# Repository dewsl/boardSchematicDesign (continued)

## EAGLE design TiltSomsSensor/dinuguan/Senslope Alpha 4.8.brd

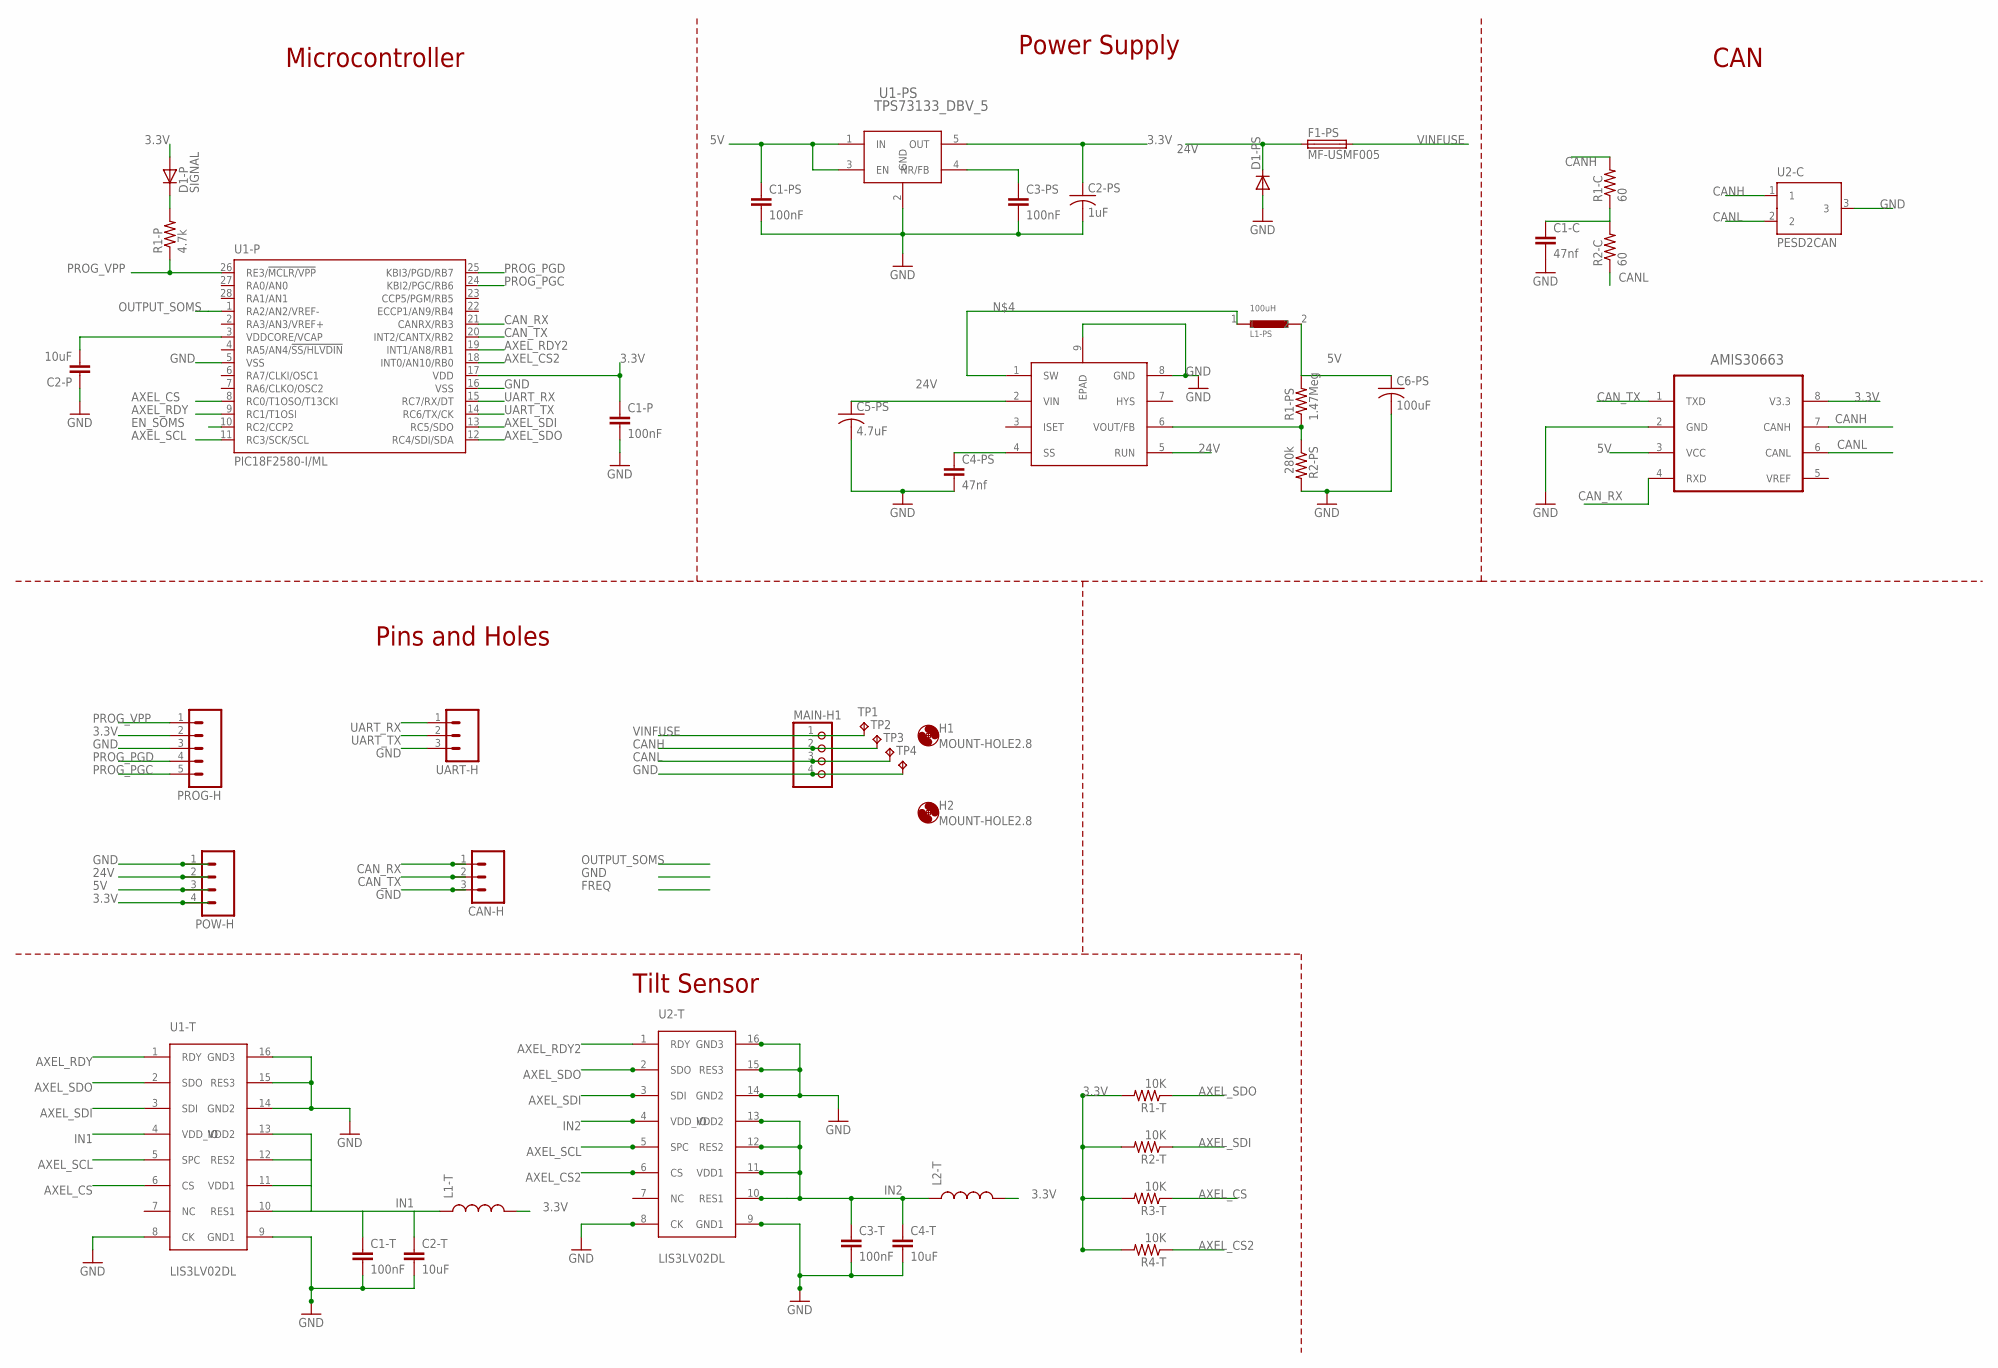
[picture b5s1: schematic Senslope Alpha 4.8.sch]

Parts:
C1-C, C4-PS: 47nf; C0805
C1-P, C1-PS, C3-PS: 100nF; C0603
C1-T, C3-T: 100nF; C0402
C2-P: 10uF; C0603
C2-PS: 1uF; C0402
C2-T, C4-T: 10uF; C0402
C5-PS: 4.7uF; C1206K
C6-PS: 100uF; C1210K
CAN-H: UART; 1X03_NO_SILK
D1-P: SIGNAL; DIODE-0603
D1-PS: DIODE-DO-214AC; DO-214AC
F1-PS: MF-USMF005; 1210
H1, H2: MOUNT-HOLE2.8; 2,8
L1-PS: 100uH; 1210
L1-T: H2; C0402
L2-T: H1; C0402
MAIN-H1: PINHD-1X04_2.54; 1X04
POW-H: M041X04_NO_SILK; 1X04_NO_SILK
PROG-H: M05PTH; 1X05
R1-C, R2-C: 60; R0805
R1-P: 4.7k; R0603
R1-PS: 1.47Meg; R0805
R1-T, R2-T, R3-T, R4-T: 10K; R0603
R2-PS: 280k; R0805
TP1, TP2, TP3, TP4: TPTP10SQ; TP10SQ
U1-P: PIC18F2580-I/ML; QFN28-ML_6X6MM
U1-PS: TPS73133_DBV_5; DBV5
U1-T, U2-T: LIS3LV02DL; LGA16
U2: AMIS30663CAN; SOIC8
U2-C: PESD2CAN; SOT23
U2-PS: LTC3631-5; MSOP8E
UART-H: UART; 1X03_NO_SILK

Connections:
3.3V: C1-P.1, C2-PS.1, D1-P.A, L1-T.2, L2-T.2, POW-H.4, PROG-H.2, R1-T.2, R2-T.2, R3-T.2, R4-T.2, U1-P.17 (VDD), U1-PS.5 (OUT), U2.8 (V3.3)
5V: C1-PS.1, C6-PS.1, L1-PS.2, POW-H.3, R1-PS.2, U1-PS.1 (IN), U1-PS.3 (EN), U2.3 (VCC)
24V: C5-PS.1, D1-PS.1 (C), F1-PS.1, POW-H.2, U2-PS.2 (VIN), U2-PS.5 (RUN)
AXEL_CS: R3-T.1, U1-P.8 (RC0/T1OSO/T13CKI), U1-T.6 (CS)
AXEL_CS2: R4-T.1, U1-P.18 (INT0/AN10/RB0), U2-T.6 (CS)
AXEL_RDY: U1-P.9 (RC1/T1OSI), U1-T.1 (RDY)
AXEL_RDY2: U1-P.19 (INT1/AN8/RB1), U2-T.1 (RDY)
AXEL_SCL: U1-P.11 (RC3/SCK/SCL), U1-T.5 (SPC), U2-T.5 (SPC)
AXEL_SDI: R2-T.1, U1-P.13 (RC5/SDO), U1-T.3 (SDI), U2-T.3 (SDI)
AXEL_SDO: R1-T.1, U1-P.12 (RC4/SDI/SDA), U1-T.2 (SDO), U2-T.2 (SDO)
CANH: MAIN-H1.2, R1-C.2, TP2.TP, U2.7 (CANH), U2-C.1
CANL: MAIN-H1.3, R2-C.1, TP3.TP, U2.6 (CANL), U2-C.2
CAN_RX: CAN-H.1, U1-P.21 (CANRX/RB3), U2.4 (RXD)
CAN_TX: CAN-H.2, U1-P.20 (INT2/CANTX/RB2), U2.1 (TXD)
EN_SOMS: U1-P.10 (RC2/CCP2)
GND: C1-C.2, C1-P.2, C1-PS.2, C1-T.2, C2-P.1, C2-PS.2, C2-T.2, C3-PS.2, C3-T.2, C4-PS.2, C4-T.2, C5-PS.2, C6-PS.2, CAN-H.3, D1-PS.2 (A), MAIN-H1.4, POW-H.1, PROG-H.3, R2-PS.2, TP4.TP, U1-P.5 (VSS), U1-P.16 (VSS), U1-PS.2 (GND), U1-T.8 (CK), U1-T.9 (GND1), U1-T.14 (GND2), U1-T.15 (RES3), U1-T.16 (GND3), U2.2 (GND), U2-C.3, U2-PS.8 (GND), U2-PS.9 (EPAD), U2-T.8 (CK), U2-T.9 (GND1), U2-T.14 (GND2), U2-T.15 (RES3), U2-T.16 (GND3), UART-H.3
IN1: C1-T.1, C2-T.1, L1-T.1, U1-T.4 (VDD_IO), U1-T.10 (RES1), U1-T.11 (VDD1), U1-T.12 (RES2), U1-T.13 (VDD2)
IN2: C3-T.1, C4-T.1, L2-T.1, U2-T.4 (VDD_IO), U2-T.10 (RES1), U2-T.11 (VDD1), U2-T.12 (RES2), U2-T.13 (VDD2)
unnamed: C1-C.1, R1-C.1, R2-C.2
unnamed: L1-PS.1, U2-PS.1 (SW)
unnamed: C3-PS.1, U1-PS.4 (NR/FB)
unnamed: R1-PS.1, R2-PS.1, U2-PS.6 (VOUT/FB)
unnamed: D1-P.C, R1-P.2
unnamed: C4-PS.1, U2-PS.4 (SS)
unnamed: C2-P.2, U1-P.3 (VDDCORE/VCAP)
OUTPUT_SOMS: U1-P.1 (RA2/AN2/VREF-)
PROG_PGC: PROG-H.5, U1-P.24 (KBI2/PGC/RB6)
PROG_PGD: PROG-H.4, U1-P.25 (KBI3/PGD/RB7)
PROG_VPP: PROG-H.1, R1-P.1, U1-P.26 (RE3/!MCLR/VPP)
UART_RX: U1-P.15 (RC7/RX/DT), UART-H.1
UART_TX: U1-P.14 (RC6/TX/CK), UART-H.2
VINFUSE: F1-PS.2, MAIN-H1.1, TP1.TP

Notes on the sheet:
Microcontroller
Power Supply
CAN
Pins and Holes
Tilt Sensor

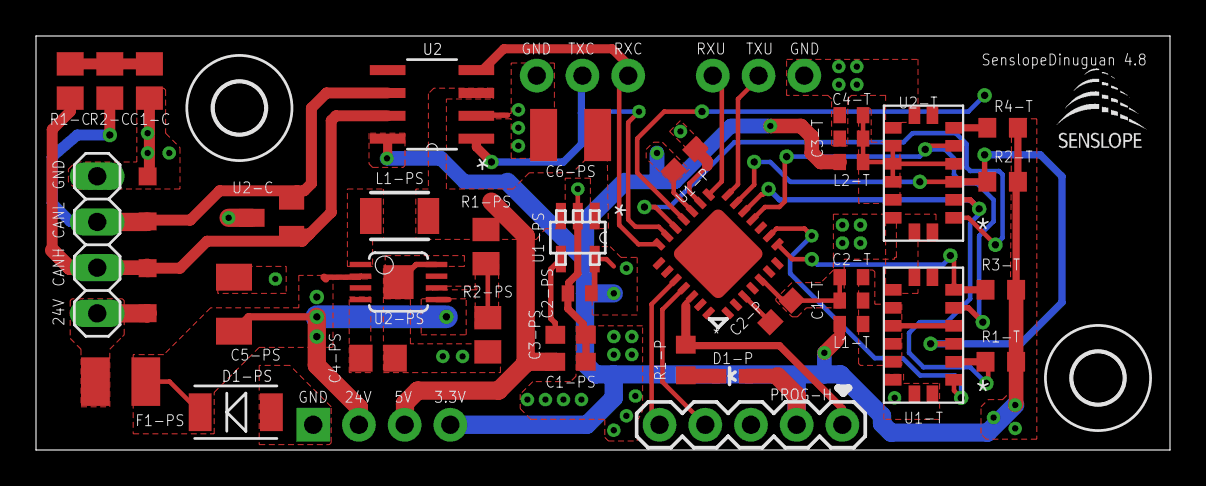
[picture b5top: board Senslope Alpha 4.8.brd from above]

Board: 2 copper layers, 63.0 x 23.0 mm, 47 parts (0 on the bottom side), 30 nets.

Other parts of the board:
U$1: LOGO_SML_TNAME

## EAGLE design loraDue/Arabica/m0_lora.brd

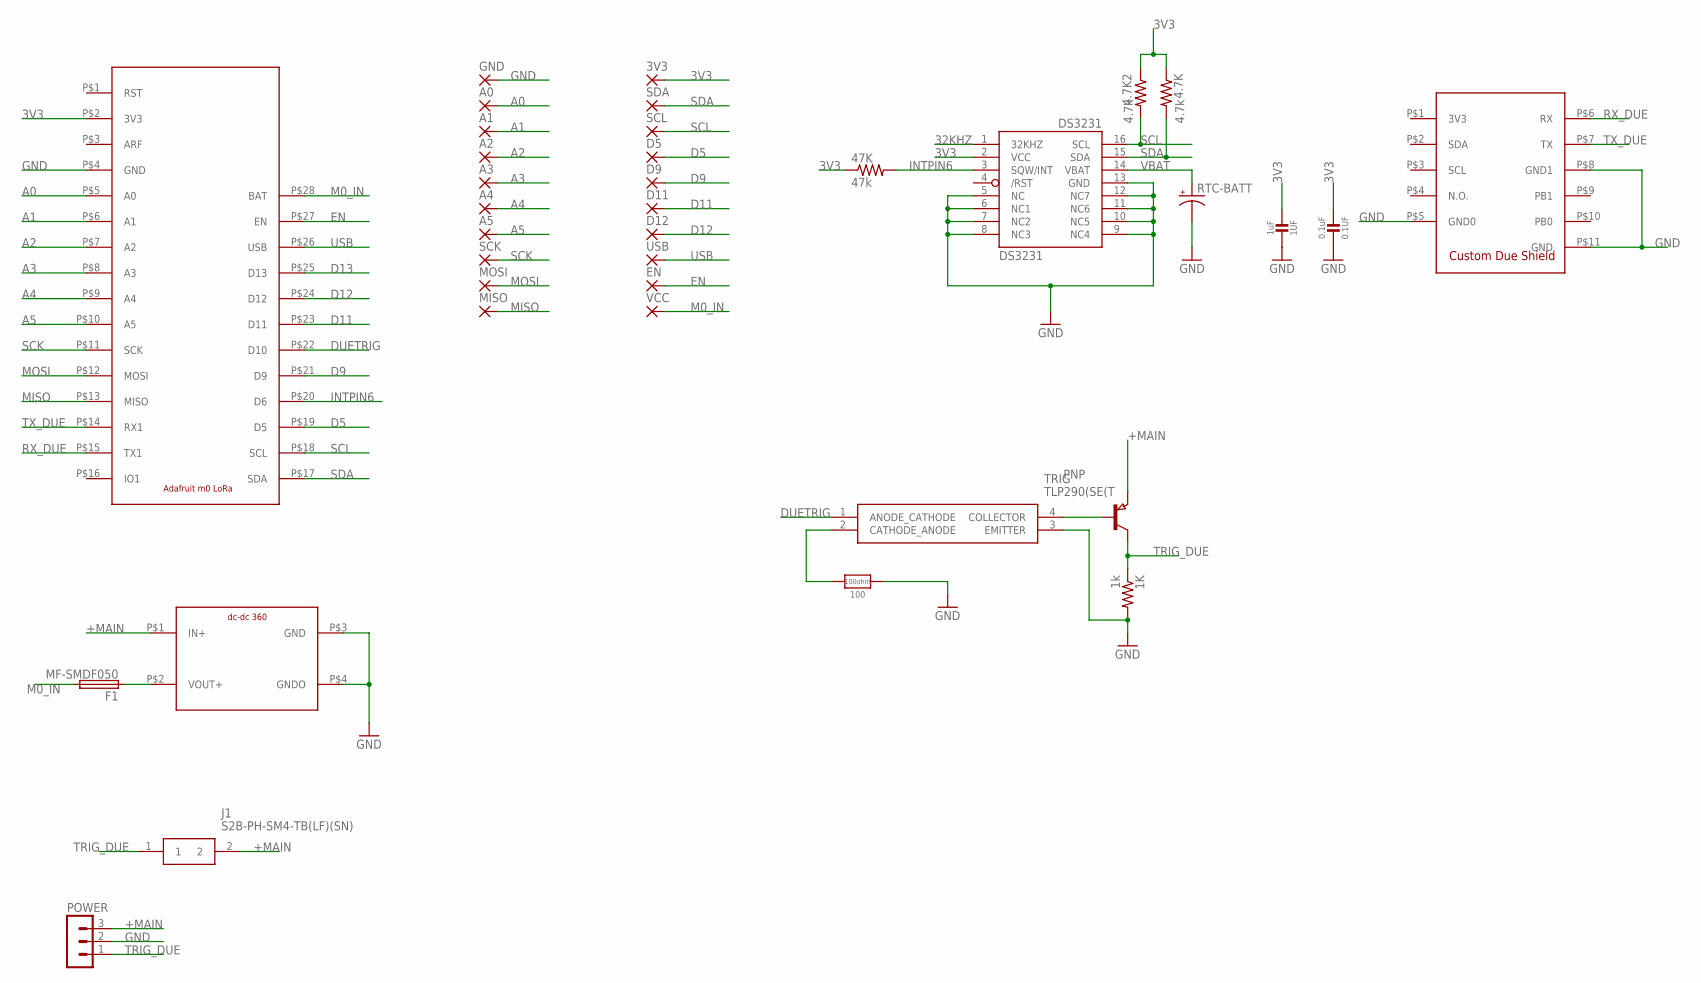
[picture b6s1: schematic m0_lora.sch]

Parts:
0.1UF: 0.1uF; 0805-NO
1K: 1k; R0805
1UF: 1uF; 0805-NO
3V3: SMD2; SMD1,27-2,54
4.7K, 4.7K2: 4.7k; R0805
47K: 47k; R0805
100: 100ohm; 0805-NO
A0, A1, A2, A3, A4, A5: SMD2; SMD1,27-2,54
D5, D9, D11, D12: SMD2; SMD1,27-2,54
DS3231: DS3231/SO; SO16W
EN: SMD2; SMD1,27-2,54
F1: MF-SMDF050
GND: SMD2; SMD1,27-2,54
J1: S2B-PH-SM4-TB(LF)(SN); S2B-PH-SM4-TB
MISO: SMD2; SMD1,27-2,54
MOSI: SMD2; SMD1,27-2,54
PNP: PNP-TRANSISTOR_SOT23; SOT23
POWER: MA03-1
RTC-BATT: CAP_POL6032; EIA6032
SCK: SMD2; SMD1,27-2,54
SCL: SMD2; SMD1,27-2,54
SDA: SMD2; SMD1,27-2,54
TRIG: TLP290(SE(T; SOIC127P700X220-4N
U$1: M0_LORA; RFM69
U$5: MINI-DC-DCDC-DC-2; MINI-DC-DC-2
U$6: DUE_PADS; DUESHIELD
USB: SMD2; SMD1,27-2,54
VCC: SMD2; SMD1,27-2,54

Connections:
3V3: 0.1UF.2, 1UF.2, 3V3.1, 4.7K.1, 4.7K2.1, 47K.1, DS3231.2 (VCC), U$1.P$2 (3V3)
32KHZ: DS3231.1 (32KHZ)
+MAIN: J1.2, PNP.2 (E), POWER.3, U$5.P$1 (IN+)
A0: A0.1, U$1.P$5 (A0)
A1: A1.1, U$1.P$6 (A1)
A2: A2.1, U$1.P$7 (A2)
A3: A3.1, U$1.P$8 (A3)
A4: A4.1, U$1.P$9 (A4)
A5: A5.1, U$1.P$10 (A5)
D5: D5.1, U$1.P$19 (D5)
D9: D9.1, U$1.P$21 (D9)
D11: D11.1, U$1.P$23 (D11)
D12: D12.1, U$1.P$24 (D12)
D13: U$1.P$25 (D13)
DUETRIG: TRIG.1 (ANODE_CATHODE), U$1.P$22 (D10)
EN: EN.1, U$1.P$27 (EN)
GND: 0.1UF.1, 1K.2, 1UF.1, 100.1, DS3231.5 (NC), DS3231.6 (NC1), DS3231.7 (NC2), DS3231.8 (NC3), DS3231.9 (NC4), DS3231.10 (NC5), DS3231.11 (NC6), DS3231.12 (NC7), DS3231.13 (GND), GND.1, POWER.2, RTC-BATT.P$2 (-), TRIG.3 (EMITTER), U$1.P$4 (GND), U$5.P$3 (GND), U$5.P$4 (GNDO), U$6.P$5 (GND0), U$6.P$8 (GND1), U$6.P$11 (GND)
INTPIN6: 47K.2, DS3231.3 (SQW/INT), U$1.P$20 (D6)
M0_IN: F1.2, U$1.P$28 (BAT), VCC.1
MISO: MISO.1, U$1.P$13 (MISO)
MOSI: MOSI.1, U$1.P$12 (MOSI)
unnamed: F1.1, U$5.P$2 (VOUT+)
unnamed: PNP.1 (B), TRIG.4 (COLLECTOR)
unnamed: 100.2, TRIG.2 (CATHODE_ANODE)
RX_DUE: U$1.P$15 (TX1), U$6.P$6 (RX)
SCK: SCK.1, U$1.P$11 (SCK)
SCL: 4.7K2.2, DS3231.16 (SCL), SCL.1, U$1.P$18 (SCL)
SDA: 4.7K.2, DS3231.15 (SDA), SDA.1, U$1.P$17 (SDA)
TRIG_DUE: 1K.1, J1.1, PNP.3 (C), POWER.1
TX_DUE: U$1.P$14 (RX1), U$6.P$7 (TX)
USB: U$1.P$26 (USB), USB.1
VBAT: DS3231.14 (VBAT), RTC-BATT.P$1 (+)

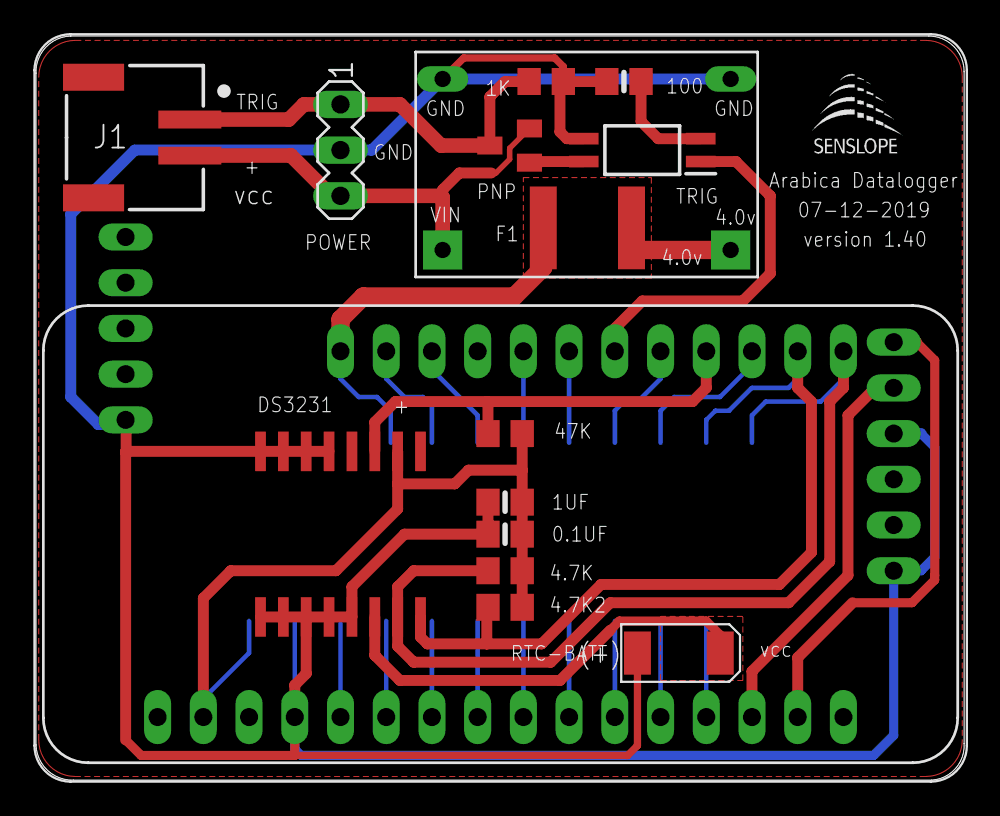
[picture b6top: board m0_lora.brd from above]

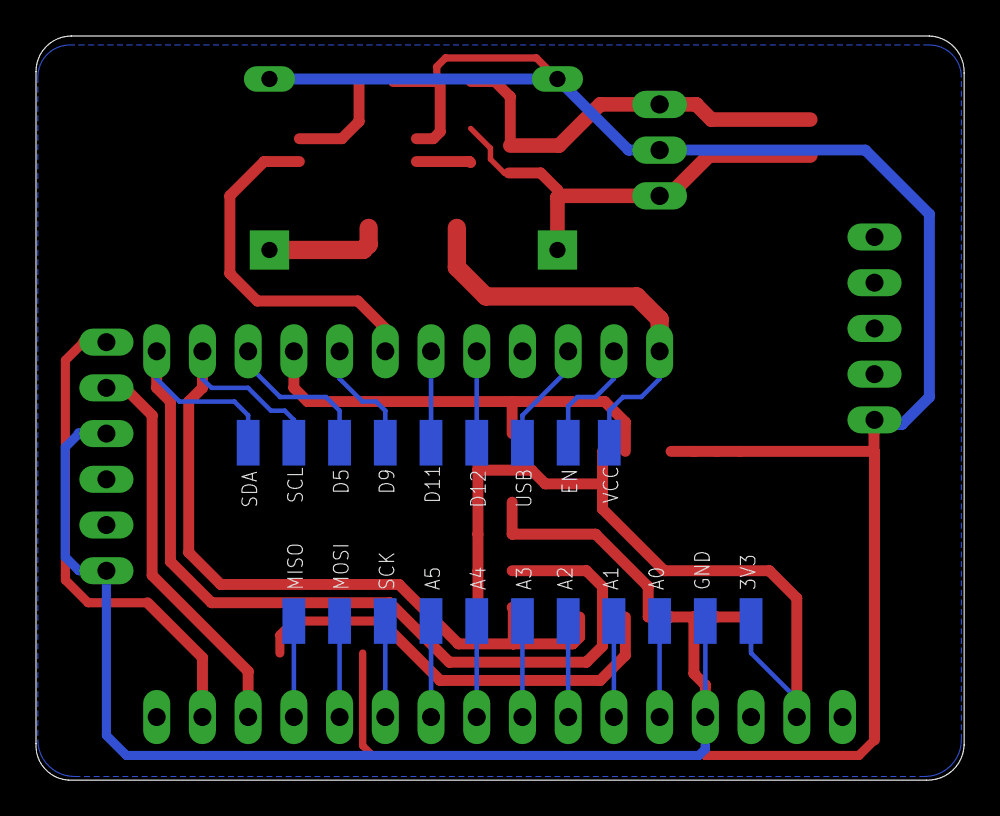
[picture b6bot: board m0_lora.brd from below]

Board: 2 copper layers, 51.6 x 41.3 mm, 38 parts (20 on the bottom side), 30 nets.

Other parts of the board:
U$2: LOGO_SML_TNAME

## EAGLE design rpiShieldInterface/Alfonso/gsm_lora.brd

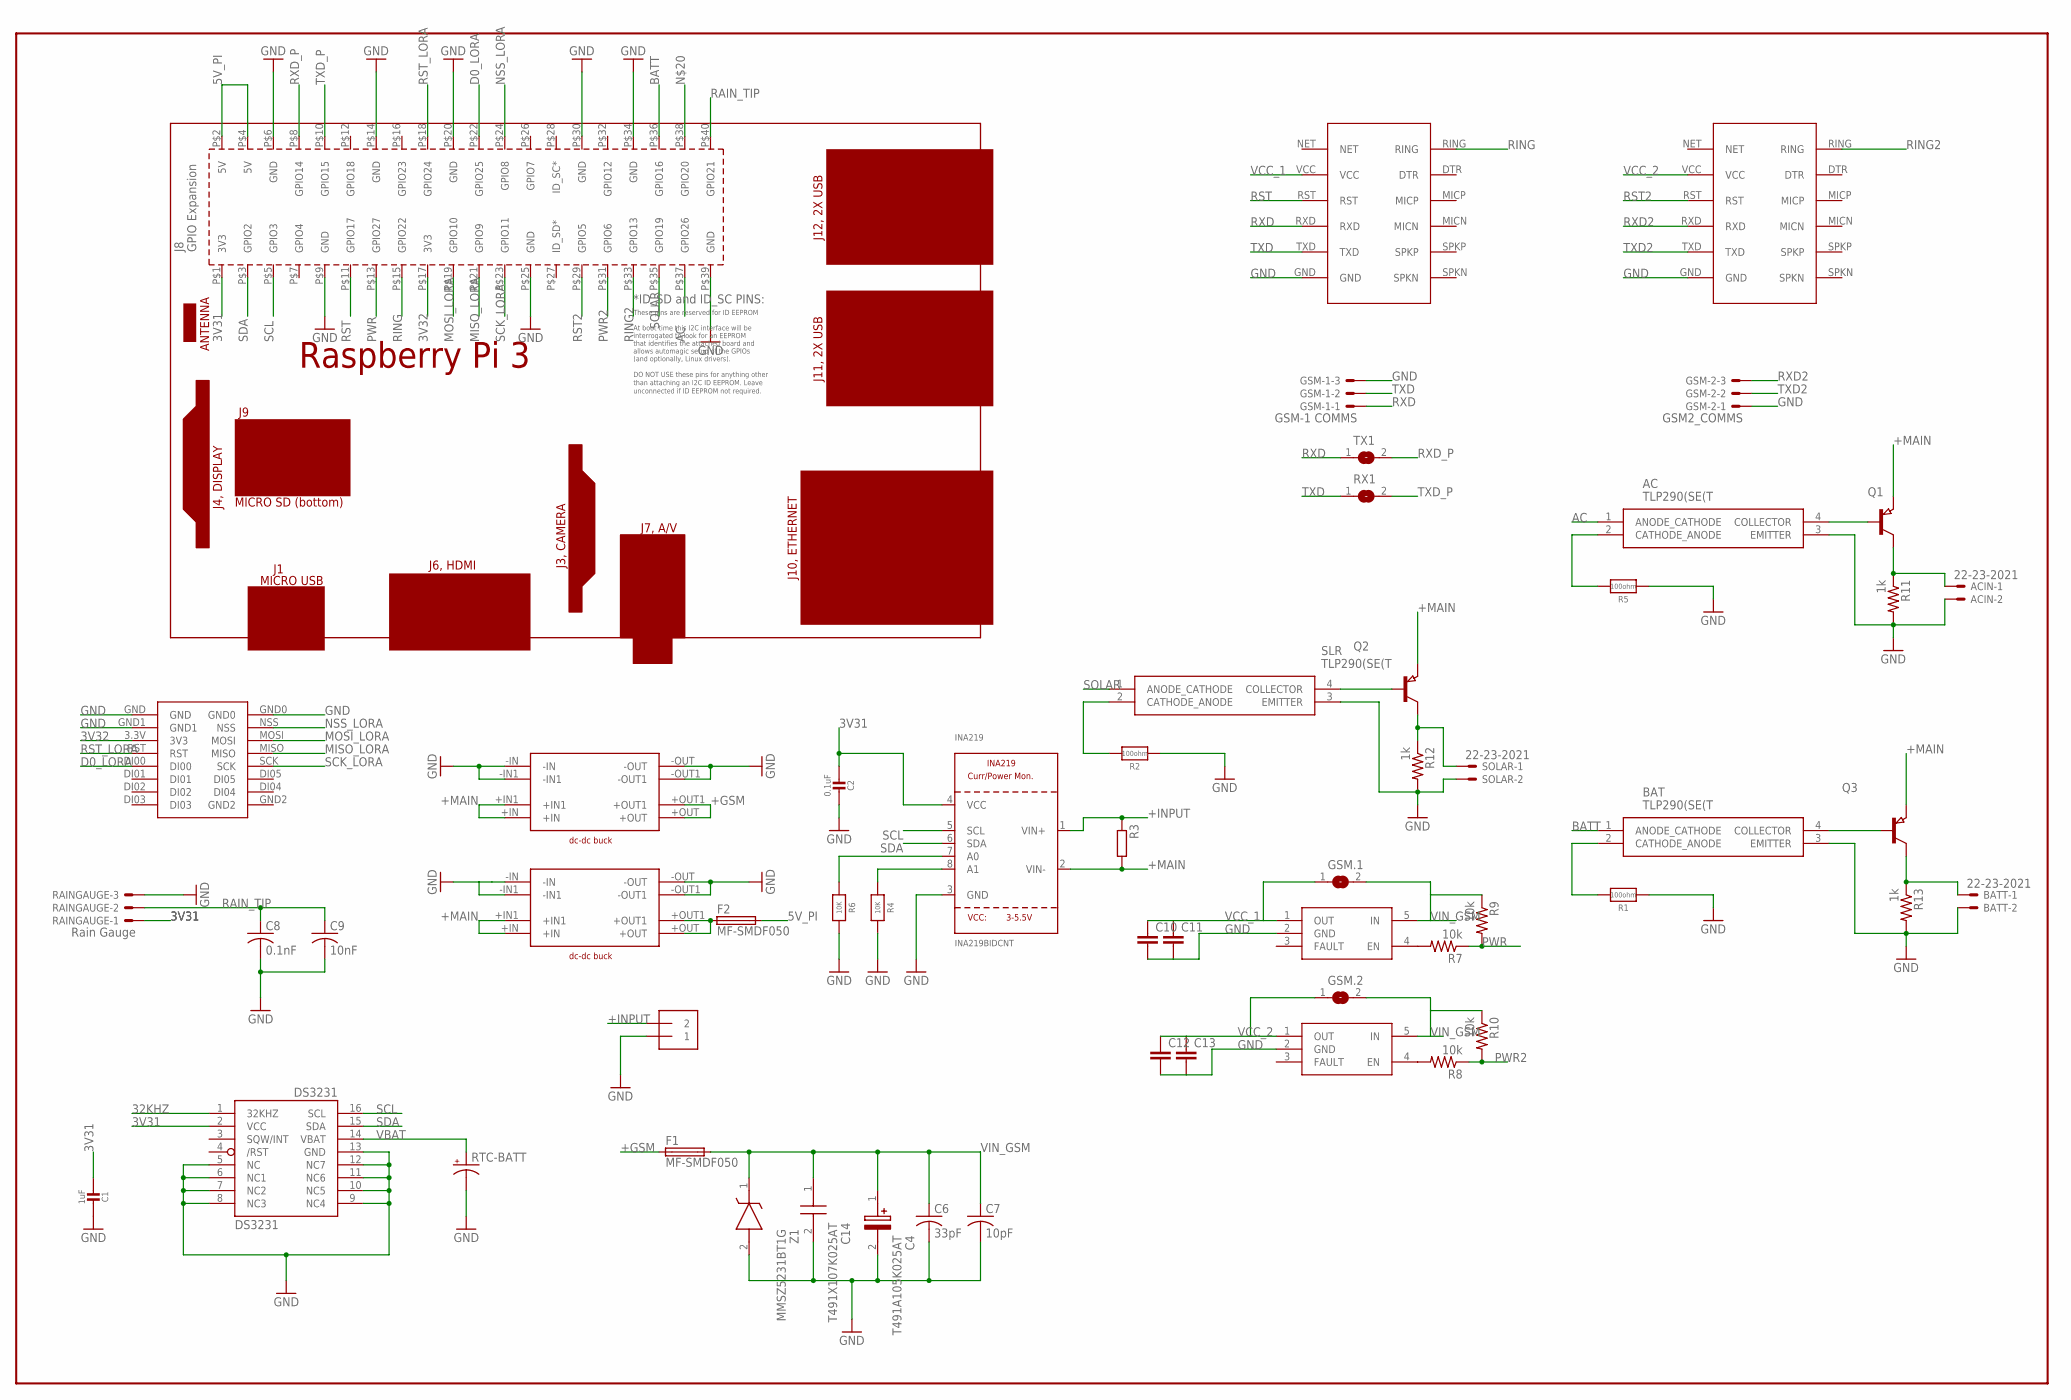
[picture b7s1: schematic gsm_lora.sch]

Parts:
AC: TLP290(SE(T; SOIC127P700X220-4N
ACIN: 22-23-2021
BAT: TLP290(SE(T; SOIC127P700X220-4N
BATT: 22-23-2021
C1: 1uF; 0805-NO
C2: 0.1uF; 0805-NO
C4: T491A105K025AT; CAPPM3216X180N
C6: 33pF; C0603
C7: 10pF; C0603
C8: 0.1nF; C0603
C9: 10nF; C0603
C10, C11, C12, C13: C-EUC4532; C4532
C14: T491X107K025AT; CAPPM7343X430N
DS3231: DS3231/SO; SO16W
F1, F2: MF-SMDF050
GSM1, GSM2: SIM800L_MODULE; SIM800L
GSM-1: GSM-1 COMMS; 22-23-2031
GSM-2: GSM2_COMMS; 22-23-2031
GSM.1, GSM.2: SJ
INA219: INA219BIDCNT; SOT23-8
POWER: TERMBLOCK_1X2-3.5MM; 1X2-3.5MM
Q1, Q2, Q3: PNP-TRANSISTOR_SOT23; SOT23
R1, R2, R5: 100ohm; 0805-NO
R3: RR2512; R2512
R4, R6: 10K; 0805-NO
R7, R8, R9, R10: 10k; R0805
R11, R12, R13: 1k; R0805
RAINGAUGE: Rain Gauge; 22-23-2031
RTC-BATT: CAP_POL1206; EIA3216
RX1: SJ
SLR: TLP290(SE(T; SOIC127P700X220-4N
SOLAR: 22-23-2021
TX1: SJ
U$1: RPI_BARE; RPI3_BARE
U$2, U$7: STMPS2161STR; SOT23-5L
U$3, U$4: DC-DC_BUCK_MAD; DC-DC_BUCK
U$6: RA-02-LORA
Z1: MMSZ5231BT1G; SOD3716X135N

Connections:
3V31: C1.2, C2.2, DS3231.2 (VCC), INA219.4 (VCC), RAINGAUGE.1, U$1.P$1 (3V3)
3V32: U$1.P$17 (3V3), U$6.3.3V (3V3)
5V_PI: F2.2, U$1.P$2 (5V), U$1.P$4 (5V)
32KHZ: DS3231.1 (32KHZ)
+GSM: F1.1, U$3.+OUT, U$3.+OUT1
+INPUT: INA219.1 (VIN+), POWER.2, R3.1
+MAIN: INA219.2 (VIN-), Q1.2 (E), Q2.2 (E), Q3.2 (E), R3.2, U$3.+IN, U$3.+IN1, U$4.+IN, U$4.+IN1
AC: AC.1 (ANODE_CATHODE), U$1.P$37 (GPIO26)
BATT: BAT.1 (ANODE_CATHODE), U$1.P$36 (GPIO16)
D0_LORA: U$1.P$22 (GPIO25), U$6.DI00
GND: AC.3 (EMITTER), ACIN.2, BAT.3 (EMITTER), BATT.2, C1.1, C2.1, C4.2 (-), C6.2, C7.2, C8.2, C9.2, C10.2, C11.2, C12.2, C13.2, C14.2, DS3231.5 (NC), DS3231.6 (NC1), DS3231.7 (NC2), DS3231.8 (NC3), DS3231.9 (NC4), DS3231.10 (NC5), DS3231.11 (NC6), DS3231.12 (NC7), DS3231.13 (GND), GSM1.GND, GSM2.GND, GSM-1.3, GSM-2.1, INA219.3 (GND), POWER.1, R1.1, R2.1, R4.2, R5.1, R6.2, R11.2, R12.2, R13.2, RAINGAUGE.3, RTC-BATT.C (-), SLR.3 (EMITTER), SOLAR.2, U$1.P$6 (GND), U$1.P$9 (GND), U$1.P$14 (GND), U$1.P$20 (GND), U$1.P$25 (GND), U$1.P$30 (GND), U$1.P$34 (GND), U$1.P$39 (GND), U$2.2 (GND), U$3.-IN, U$3.-IN1, U$3.-OUT, U$3.-OUT1, U$4.-IN, U$4.-IN1, U$4.-OUT, U$4.-OUT1, U$6.GND, U$6.GND0, U$6.GND1, U$7.2 (GND), Z1.2 (A)
MISO_LORA: U$1.P$21 (GPIO9), U$6.MISO
MOSI_LORA: U$1.P$19 (GPIO10), U$6.MOSI
unnamed: INA219.8 (A1), R4.1
unnamed: INA219.7 (A0), R6.1
unnamed: R2.2, SLR.2 (CATHODE_ANODE)
unnamed: AC.4 (COLLECTOR), Q1.1 (B)
unnamed: ACIN.1, Q1.3 (C), R11.1
unnamed: BAT.2 (CATHODE_ANODE), R1.2
unnamed: BAT.4 (COLLECTOR), Q3.1 (B)
unnamed: Q2.1 (B), SLR.4 (COLLECTOR)
unnamed: BATT.1, Q3.3 (C), R13.1
unnamed: R7.2, U$7.4 (EN)
unnamed: R8.2, U$2.4 (EN)
unnamed: AC.2 (CATHODE_ANODE), R5.2
unnamed: Q2.3 (C), R12.1, SOLAR.1
unnamed: F2.1, U$4.+OUT, U$4.+OUT1
NSS_LORA: U$1.P$24 (GPIO8), U$6.NSS
PWR: R7.1, R9.2, U$1.P$13 (GPIO27)
PWR2: R8.1, R10.2, U$1.P$31 (GPIO6)
RAIN_TIP: C8.1, C9.1, RAINGAUGE.2, U$1.P$40 (GPIO21)
RING: GSM1.RING, U$1.P$15 (GPIO22)
RING2: GSM2.RING, U$1.P$33 (GPIO13)
RST: GSM1.RST, U$1.P$11 (GPIO17)
RST2: GSM2.RST, U$1.P$29 (GPIO5)
RST_LORA: U$1.P$18 (GPIO24), U$6.RST
RXD: GSM1.RXD, GSM-1.1, TX1.1
RXD2: GSM2.RXD, GSM-2.3
RXD_P: TX1.2, U$1.P$8 (GPIO14)
SCK_LORA: U$1.P$23 (GPIO11), U$6.SCK
SCL: DS3231.16 (SCL), INA219.5 (SCL), U$1.P$5 (GPIO3)
SDA: DS3231.15 (SDA), INA219.6 (SDA), U$1.P$3 (GPIO2)
SOLAR: SLR.1 (ANODE_CATHODE), U$1.P$35 (GPIO19)
TXD: GSM1.TXD, GSM-1.2, RX1.1
TXD2: GSM2.TXD, GSM-2.2
TXD_P: RX1.2, U$1.P$10 (GPIO15)
VBAT: DS3231.14 (VBAT), RTC-BATT.A (+)
VCC_1: C10.1, C11.1, GSM1.VCC, GSM.1.1, U$7.1 (OUT)
VCC_2: C12.1, C13.1, GSM2.VCC, GSM.2.1, U$2.1 (OUT)
VIN_GSM: C4.1 (+), C6.1, C7.1, C14.1, F1.2, GSM.1.2, GSM.2.2, R9.1, R10.1, U$2.5 (IN), U$7.5 (IN), Z1.1 (K)

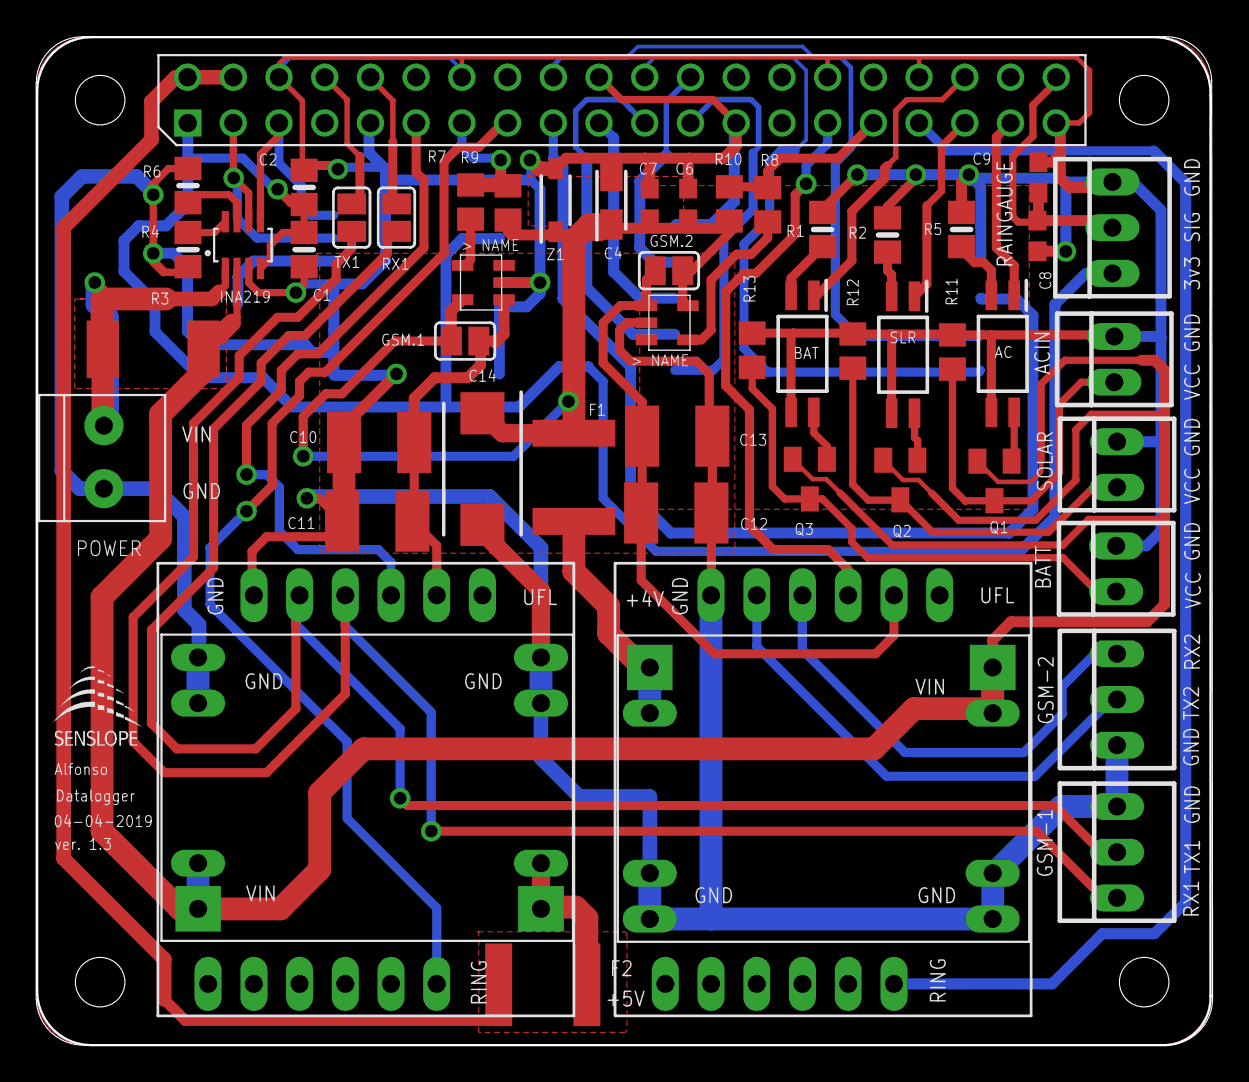
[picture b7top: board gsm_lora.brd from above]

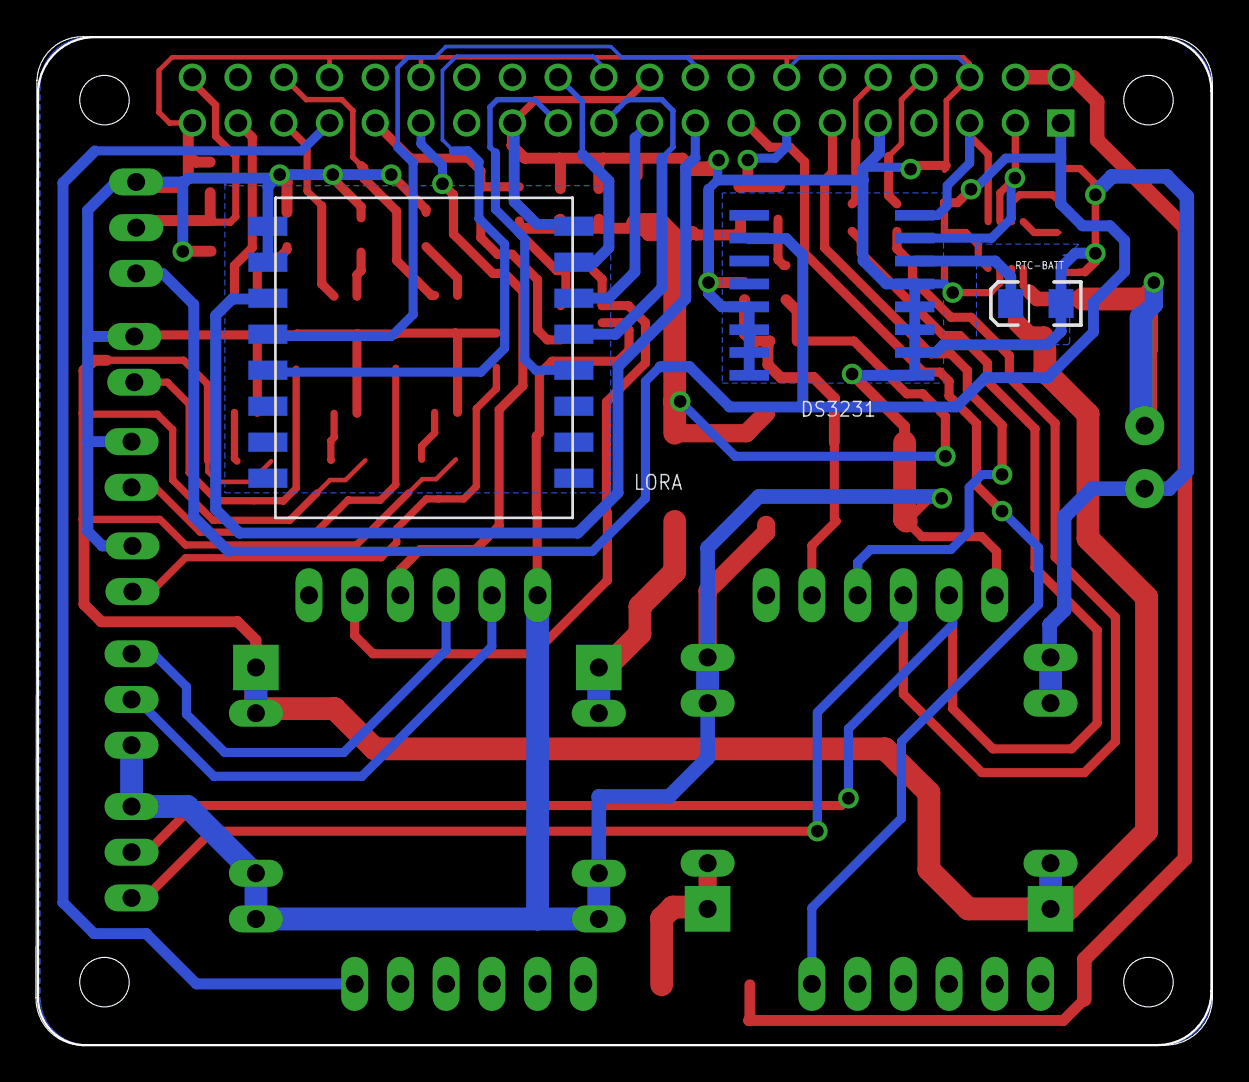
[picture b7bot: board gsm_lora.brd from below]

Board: 2 copper layers, 65.4 x 56.0 mm, 57 parts (3 on the bottom side), 49 nets.

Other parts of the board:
U$5: LOGO_SML_TNAME
